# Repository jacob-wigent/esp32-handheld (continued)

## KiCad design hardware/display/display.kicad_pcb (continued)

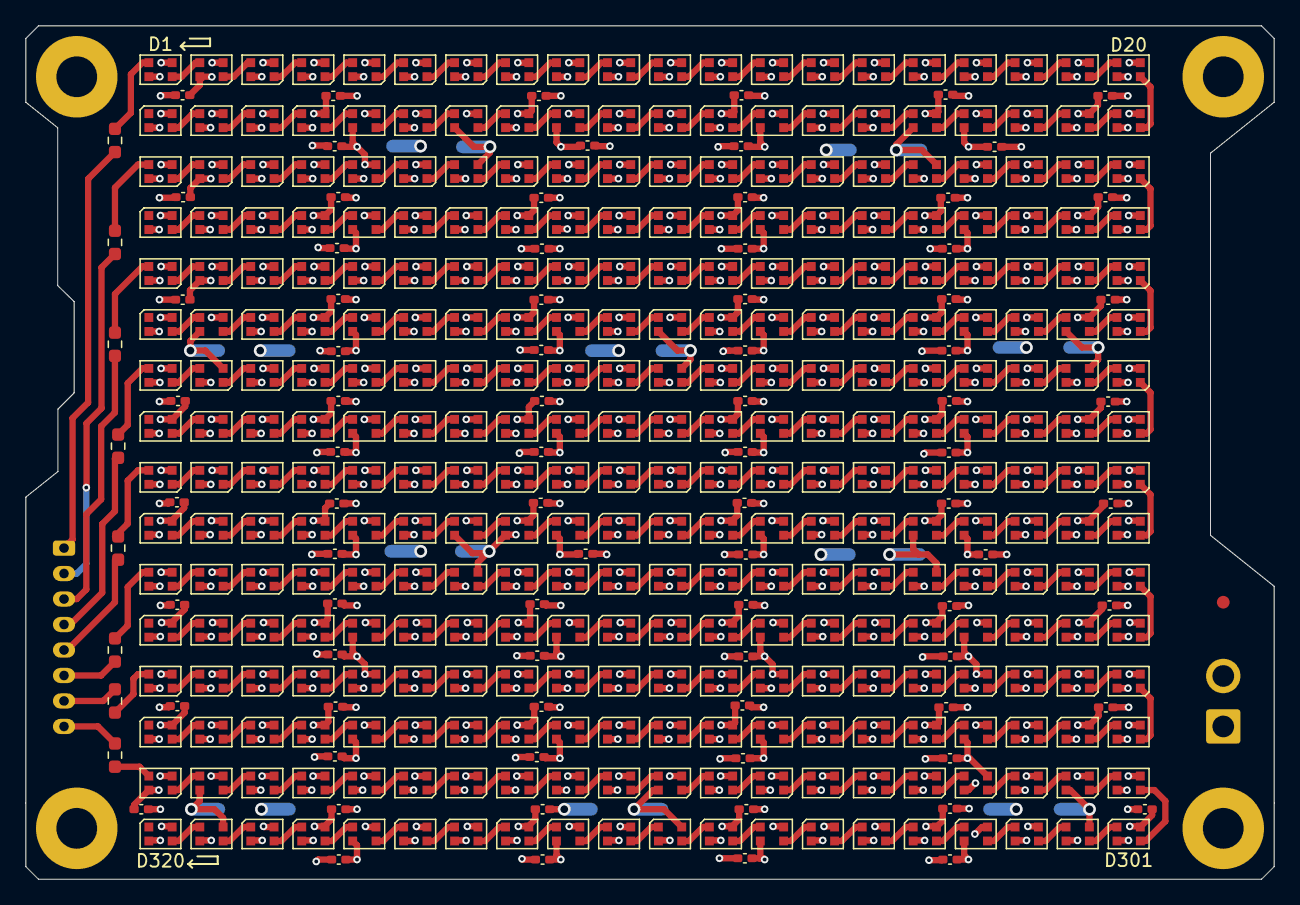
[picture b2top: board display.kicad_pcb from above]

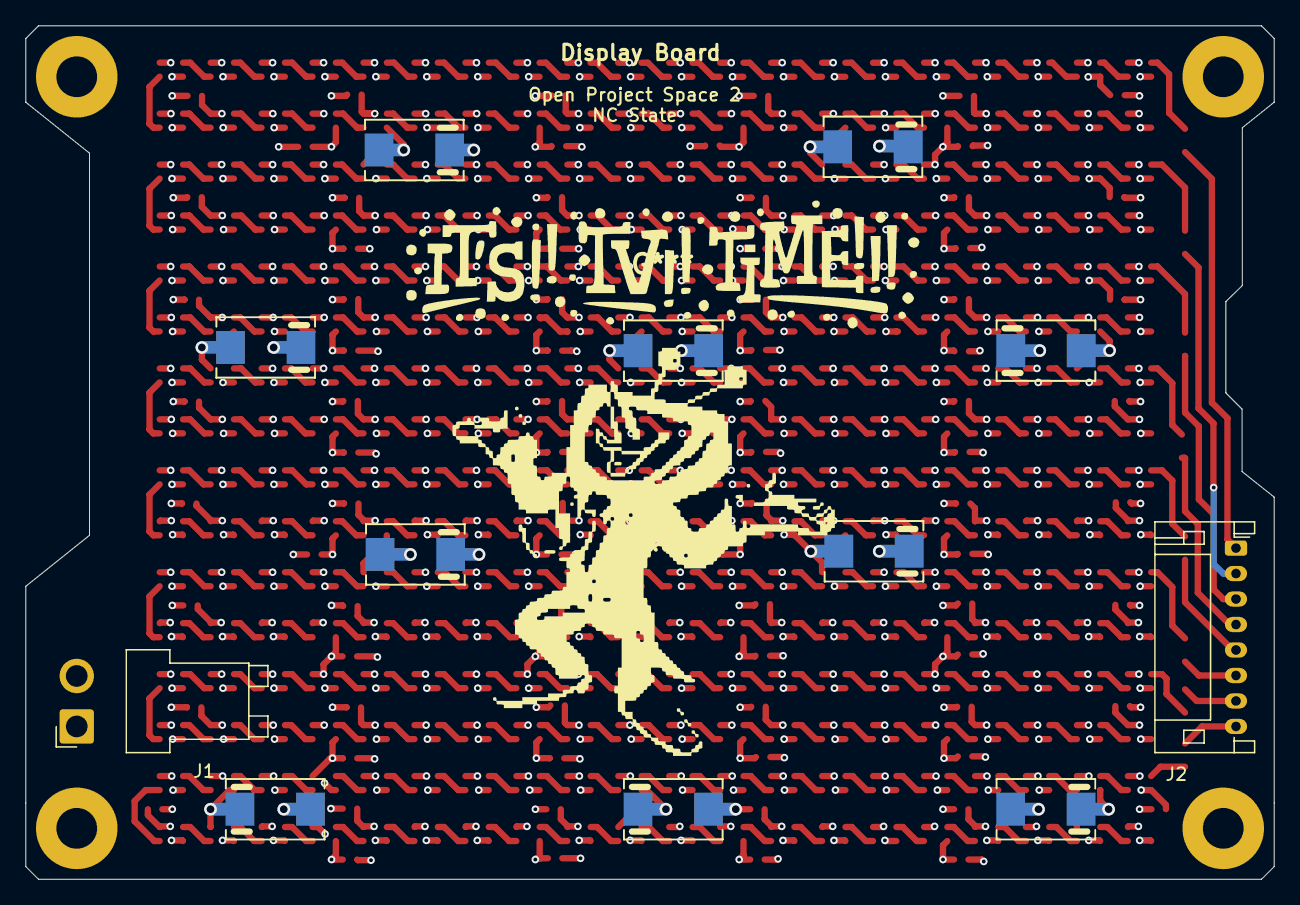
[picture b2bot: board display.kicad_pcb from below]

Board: 4 copper layers, 98.0 x 67.0 mm, 425 parts (12 on the bottom side), 330 nets.

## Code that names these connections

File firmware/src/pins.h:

#pragma once
#include "driver/gpio.h"

// ----- INPUTS -----
// Tech
#define SELECT      GPIO_NUM_0
#define BOOT        GPIO_NUM_0
#define START       GPIO_NUM_2
// Controls
#define RIGHT       GPIO_NUM_17
#define UP          GPIO_NUM_18
#define DOWN        GPIO_NUM_36
#define LEFT        GPIO_NUM_35
#define A           GPIO_NUM_39
#define B           GPIO_NUM_40
#define X           GPIO_NUM_41
#define Y           GPIO_NUM_42
#define BUMPER_L    GPIO_NUM_37
#define BUMPER_R    GPIO_NUM_38
#define STICK_BTN   GPIO_NUM_15
#define AY          GPIO_NUM_6
#define AX          GPIO_NUM_7

// ----- OUTPUTS -----
// Status LED
#define STATUS_LED  GPIO_NUM_3
// Speaker
#define SPEAKER     GPIO_NUM_45
// Motor
#define MOTOR       GPIO_NUM_46

// ----- PERIPHERALS -----
// I2C Pins
#define SDA         GPIO_NUM_8
#define SCL         GPIO_NUM_9
// Display Pins
#define DISP8       GPIO_NUM_10
#define DISP7       GPIO_NUM_11
#define DISP6       GPIO_NUM_12
#define DISP5       GPIO_NUM_13
#define DISP4       GPIO_NUM_14
#define DISP3       GPIO_NUM_21
#define DISP2       GPIO_NUM_47
#define DISP1       GPIO_NUM_48

// ----- POWER MONITORING -----
// Battery
#define ABAT        GPIO_NUM_1
#define CHG_STAT    GPIO_NUM_16
// USB-C
#define ACC1        GPIO_NUM_4
#define ACC2        GPIO_NUM_5

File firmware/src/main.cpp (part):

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  
  pinMode(StatusLED, OUTPUT);
  digitalWrite(StatusLED, HIGH);
  pinMode(ChgStat, INPUT);

  analogReadResolution(12);
  analogSetAttenuation(ADC_11db);
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  pinMode(Y, INPUT_PULLUP);
  pinMode(START, INPUT_PULLUP);
  pinMode(SELECT, INPUT_PULLUP);
  pinMode(StckBtn, INPUT_PULLUP);

  int sampleAX = analogRead(AX);
  int sampleAY = analogRead(AY);
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    raw_adc /= 8;
    float battery_v = readBatteryVoltage();

    // Read CC pins (ACC1/ACC2) — they are through 100k/100k dividers (x2 to get actual)
    uint32_t cc1_mv = readAnalogMilliVoltsAvg(ACC1, 8);
    uint32_t cc2_mv = readAnalogMilliVoltsAvg(ACC2, 8);
    float cc1_v_actual = (cc1_mv / 1000.0f) * 2.0f;
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    // Choose active CC line (the higher voltage is the active orientation). Require a small threshold.
    float active_cc_v = 0.0f;
    const char *active_pin = "none";
    if (cc1_v_actual > cc2_v_actual + 0.02f && cc1_v_actual > 0.05f) { active_cc_v = cc1_v_actual; active_pin = "ACC1"; }
    else if (cc2_v_actual > cc1_v_actual + 0.02f && cc2_v_actual > 0.05f) { active_cc_v = cc2_v_actual; active_pin = "ACC2"; }
    else {
      // If nearly equal but non-zero, pick the larger
      if (cc1_v_actual >= cc2_v_actual && cc1_v_actual > 0.05f) { active_cc_v = cc1_v_actual; active_pin = "ACC1"; }
      else if (cc2_v_actual > 0.05f) { active_cc_v = cc2_v_actual; active_pin = "ACC2"; }
    }

    const char *advert = classifyCCAdvertised(active_cc_v);
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
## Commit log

2025-09-29 Project Setup
    Added empty KiCad project for display PCB and empty PlatformIO project for OPS2 ESP32-S3 dev-board
2025-09-29 Started Display Schematic
    Added a hierarchal sheet for a 2x20 section of the display.
2025-10-01 Added Schematic
2025-10-07 USB Interface and Started Power Management
2025-10-07 Basic Microcontroller Stuff and Display Power
2025-10-07 Changed GitIgnore
2025-10-07 Added Libraries
2025-10-07 Updated GitIgnore
    Changed Gitignore to ignore backup generation
2025-10-07 Fixed Capacitors
2025-10-08 Added USB C Power Monitoring and Start/Select
    also renamed project
2025-10-08 Updated GPIOs
2025-10-08 Added Joystick
2025-10-08 Moved Libraries
2025-10-08 Added Joystick Symbol/Footprint
2025-10-08 Updated Custom Component Lib Sources
2025-10-09 GPIOs
2025-10-09 Started Display Layout
2025-10-09 Arranged LEDs
    Arranged NeoPixel footprints and handled schematic/PCB link and designations
2025-10-09 Basic Display PCB Layout
2025-10-09 Added Silkscreen Screw Outlines
2025-10-09 Fixed Screw Outlines
2025-10-10 Added PCB cutout for display board, accommodating power JST connector
2025-10-15 Added some notes
2025-10-15 Added 1000uF Cap Model
2025-10-15 Added Connector Models
    Instructions included on how to import into KiCad library
2025-10-15 Display Traces and Connector Placement
    Board is all connected and has no errors
2025-10-15 Moved Silkscreen Reference
2025-10-16 Data Line Cleanup
    Moved some resistors and removed old, unnecessary vias.
2025-10-16 Will Meeting
    Added JLC constraints
2025-10-17 Fixed outline
2025-10-17 Modified README, updated 3D models
2025-10-21 Added assembly part numbers and schematic caps
    Linked LCSC part numbers for LEDs, decoupling caps, and data resistors.
    Added 10, 100uF caps in schematic, but footprints are needed still.
2025-10-22 Added Motherboard PCB edge cut, added some footprints
2025-10-22 FIXED LIBRARIES!!!!!
2025-10-22 Updated LED 3D model
2025-10-22 Added footprints in motherboard, preparing for PCB layout
2025-10-22 Added 100uF cap symbols and footprints
    Added symbols in schematic and footprints in PCB. Caps need layout and routing.
2025-10-22 Arranged/Routed 100uF Bulk Caps
    Manually routed each of the 10 caps by deleting 2 common NoePixel vias to make room for the pad, orienting the cap so VDD/GND is next to the deleted vias, and then routed VDD/GND into the one big via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
2025-10-22 Fixed a Via and Updated Silkscreen
    Changed one via position and added lines to indicate positive side of tant cap on silkscreen.
2025-10-23 Charger, Started GPIO Assignments
    Added ESP32 devboard charger circuit and began assigning GPIOs. Provided lots of annotations and justifications for GPIO assignments.
2025-10-23 JLC Build FIles
2025-10-25 Motherboard Minor Annotation Updates
2025-10-25 Added CC Voltage Divider and Updated Charge LED Resistor
2025-10-27 JLC Parts Update
2025-10-27 Started Motherboard PCB Layout
2025-10-27 Cont. Motherboard Layout
2025-10-28 Routing 💀
    Layout and routing. Used 3v3 plane to route some power traces.
    Also added full size joystick model and footprint and schematic.
2025-10-28 Added dimension drawings to display board
2025-10-28 Added Real Mounting Holes and Fiducial
2025-10-28 Will Notes
2025-10-28 lowkey idk
2025-10-28 Added Side Mount Button
2025-10-29 Updated motherboard, buttons are set, dimensions are visible
2025-10-29 Moved Test Points
2025-10-30 Added bumper buttons
2025-10-30 Adjusted Bumper Button Positions
2025-10-30 12mm Corners
2025-10-30 Update gitignore
2025-10-30 Adjusted Data Traces
    Made display data traces and SDA/SCL a little thinner
2025-10-30 Reset Button
    SMD Reset button on back behind MCU
2025-10-30 Added IMU Model
2025-10-30 Moved ABat Voltage Divider
2025-10-30 Added header file that defines our current pins
2025-10-30 Right Side Controls Routing
2025-10-30 Routed Joystick
2025-10-30 Routed Charge Stat to MCU
2025-10-30 Labelled Test Points
2025-10-30 Labelled power connectors on Motherboard
2025-10-30 Updated Schematic, Added motor/speaker connector
2025-10-30 Updated Mounting Holes
    M2 screw holes for M2x4mm screws into top of case.
2025-10-30 Added ucbc 3d model
2025-10-30 Updated Motherboard
2025-10-31 Routing
2025-10-31 Updated Mounting Holes
    Made display holes M3
    Matching hole pattern on motherboard to mount display.
    Distributed 4, M3 mounting holes throuhout motherboard
2025-10-31 Added status LED trace
2025-10-31 Modify motherboard
2025-10-31 Motherboard Traces
2025-10-31 Expanded Mouting hole Margins, modified traces
2025-11-03 WIP Motherboard and Display Revisions
2025-11-03 WIP Continued – Display
2025-11-03 Display done
2025-11-03 Adjusted Button position on display
2025-11-03 Modified Display Traces
    Added space between display data traces where they were very close to other traces/pads.
    Increased size of traces from bulk caps to vias.
2025-11-03 Small changes to motherboard traces
2025-11-03 Updated Motherboard and Minor Display Changes
    Updated Joystick Position, Moved Display Board Port
    other small fixes
2025-11-04 Add README and update pin definitions; implement LED control and animation patterns
2025-11-04 ERC and DRC Checks
    Made slight modifications to schematics and layouts to ensure ERCs and DRCs pass on both boards.
    Made some exclusions for irrelevant warnings.
2025-11-04 Confirmed Thermal Reliefs and Re-filled Zones
2025-11-04 Konami
2025-11-04 Stickers 🤩
    Added sticker footprints
2025-11-04 Added silkscreen graphics
2025-11-04 Finalized board, added art, ready to submit
2025-11-04 DFM Checks Passed, Board Submitted
2025-11-05 Continued software testing
2025-11-05 Moved non-native step files into project library folder
2025-11-19 White at 50% Demo
2025-11-19 Added battery charging serial outputs for debugging MCP73831
2025-11-20 Updated code
2025-11-21 AI Slopped Demo Code
2025-11-21 Demo slop working as expected
2025-11-22 Adjusted Breakout
    Made stick adjust paddle velocity rather than position. Increased number of rows of bricks.
2025-11-25 Added Models for Power Components
2025-11-28 Some improvements to menu navigation, added flappy bird and tetris
2025-11-28 Updated 3d models for motherboard
2025-11-29 Added battery logging to demo
2025-11-29 Quick modifications to add a high-side pmos switch between the battery and the display board
2025-12-01 Update .gitignore
    Added photos locally, ignoring for repo
2025-12-01 Battery and CC Logging
2025-12-30 ESP-IDF Setup
2026-05-13 Blink
2026-05-14 Begin custom Neopixel driver
2026-05-14 Achieve proof of concept Neopixel driver
2026-05-14 Finish RMT Neopixel driver
    RMT method works but only for 4 segments. Alternative method will be necessary to achieve 8-way control.
2026-05-14 Fix temp display ranges
